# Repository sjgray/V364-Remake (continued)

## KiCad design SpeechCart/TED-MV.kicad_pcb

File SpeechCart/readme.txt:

Commodore V364 Prototype Remake Project   Steve J. Gray
=======================================

This is a project to remake the V364 prototype computer from Commodore.
This would have been the flagship model in the TED/264 series, and
would feature a larger case with numeric keypad and built-in speech
synthesis using a more integrated version of the Magic Voice cartridge
that was released for the C64.

Speech Cartridge
----------------

This is a cartridge to aid in development of the custom Gate Array chip
which this PCB will not work without. It uses the same circuit as the
V364 computer but is not guaranteed to be correct. It has a ROM socket
for development code and an audio jack for output via TRS cable. If not
plugged in audio will be routed thru the cartridge port and mixed with
the regular computer audio.

*** IMPORTANT!!!!!!!!! ***

This cart is untested! Use at own risk!!!!! Unless you are willing
to help with development of the custom gate array this PCB will be
of no use!

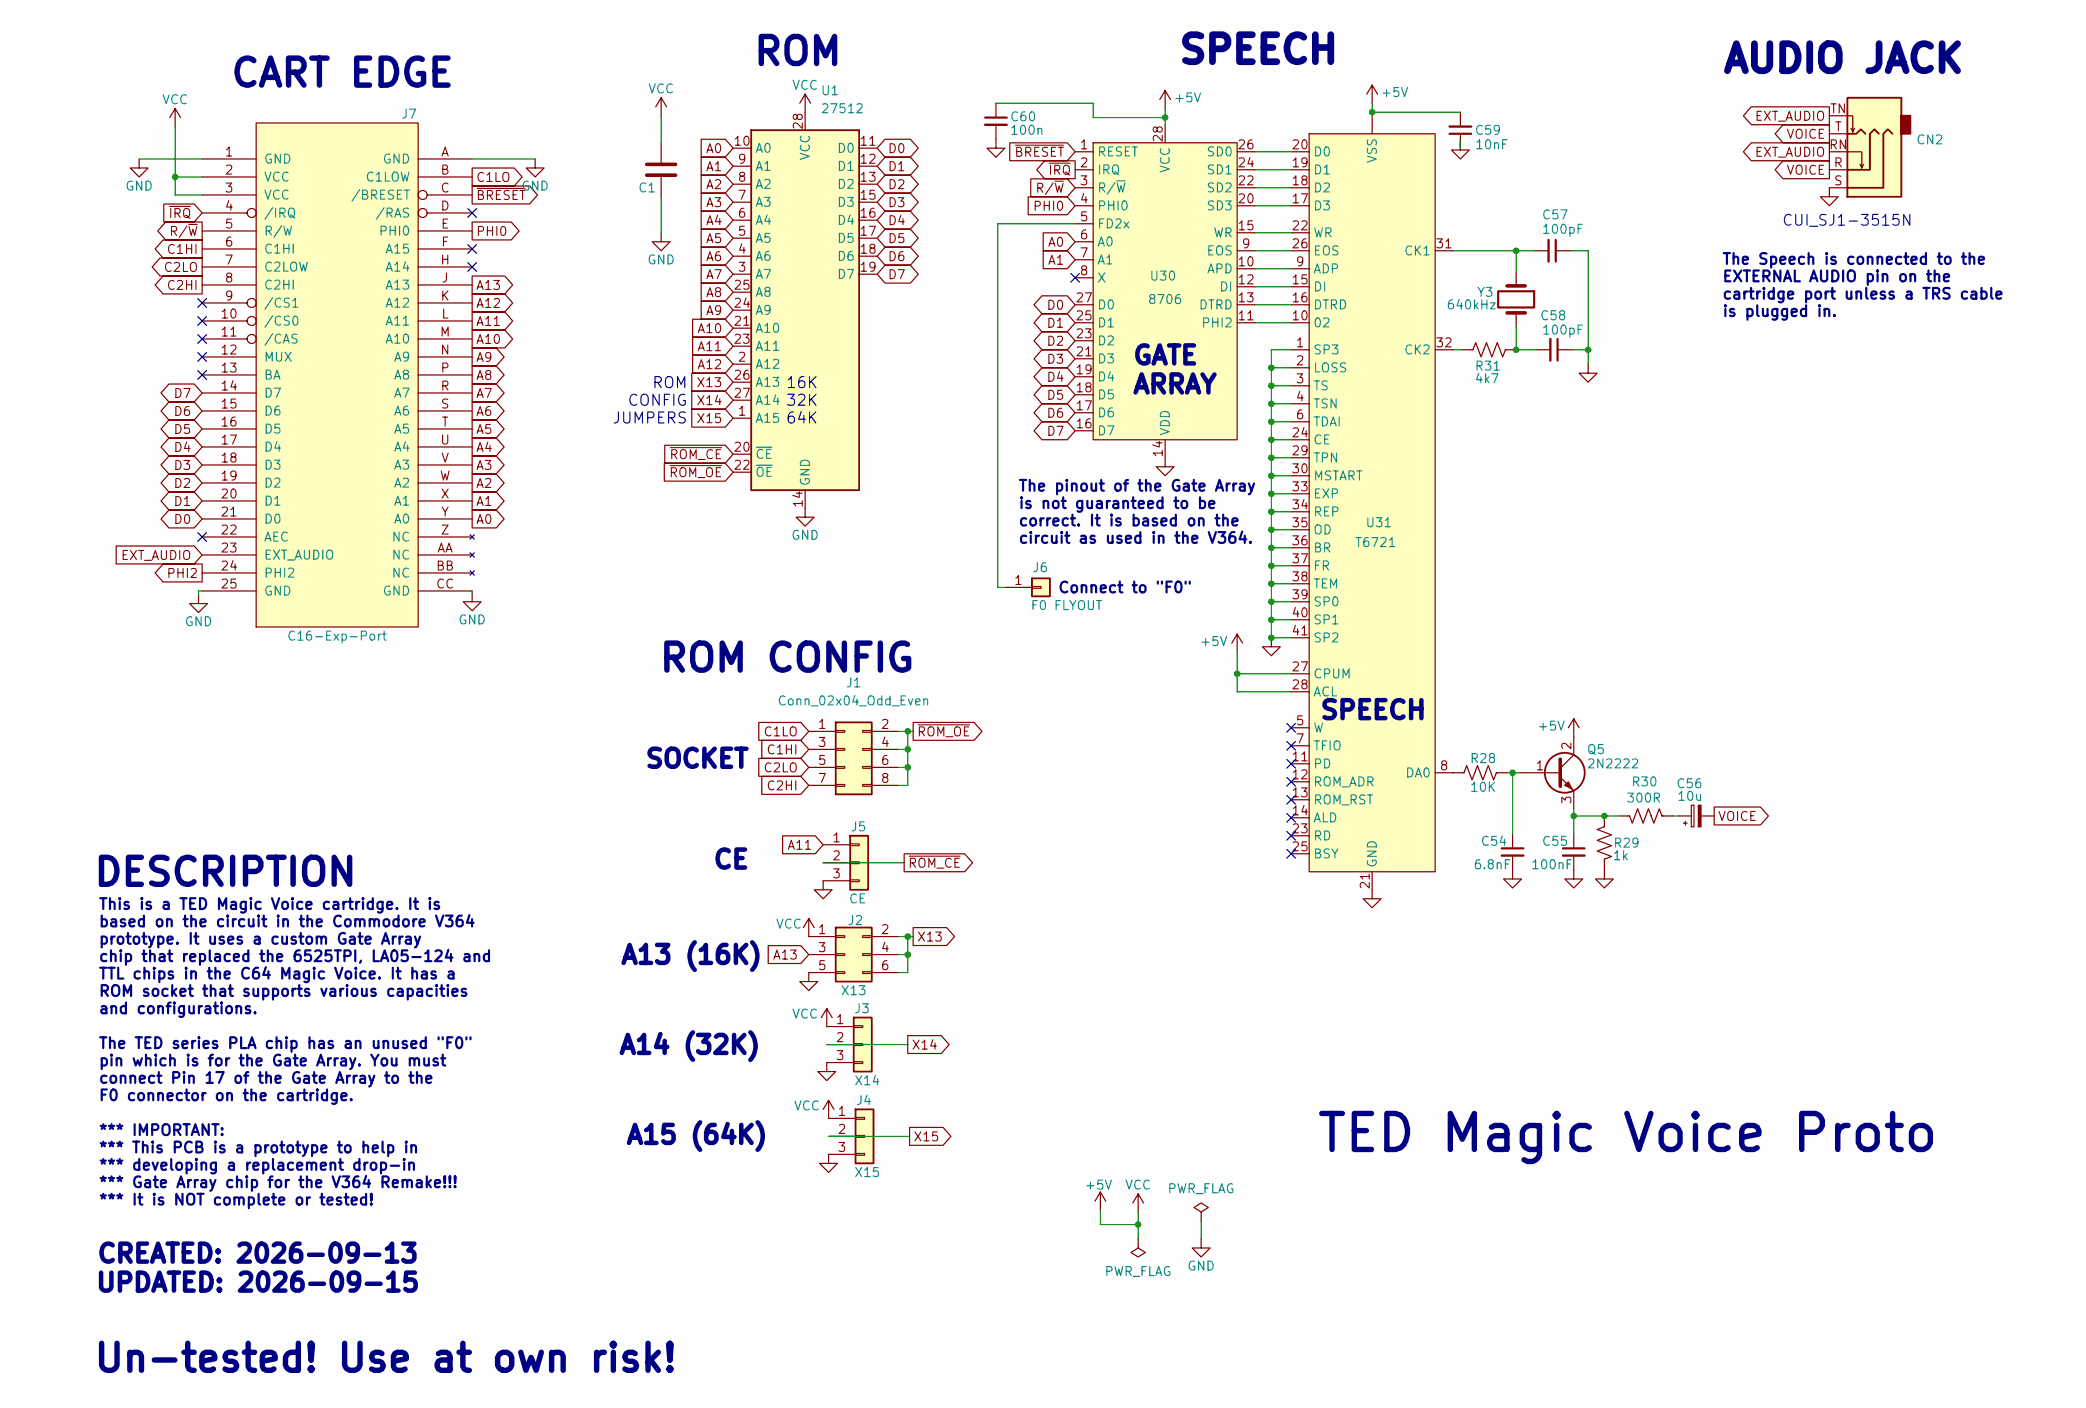
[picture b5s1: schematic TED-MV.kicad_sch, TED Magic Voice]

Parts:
C1: C; C_Disc_D5.0mm_W2.5mm_P5.00mm
C54: 6.8nF; C_Disc_D5.0mm_W2.5mm_P5.00mm
C55: 100nF; C_Disc_D5.0mm_W2.5mm_P5.00mm
C56: 10u; C_Disc_D5.0mm_W2.5mm_P5.00mm
C57, C58: 100pF; C_Disc_D5.0mm_W2.5mm_P5.00mm
C59: 10nF; C_Disc_D5.0mm_W2.5mm_P5.00mm
C60: 100n; C_Disc_D5.0mm_W2.5mm_P5.00mm
CN2: AUDIO_OUT; Jack_3.5mm_CUI_SJ1-3515N_Horizontal; MouserPN 490-SJ1-3525N
J1: Conn_02x04_Odd_Even; PinHeader_2x04_P2.54mm_Vertical
J2: X13; PinHeader_2x03_P2.54mm_Vertical
J3: X14; PinHeader_1x03_P2.54mm_Vertical
J4: X15; PinHeader_1x03_P2.54mm_Vertical
J5: CE; PinHeader_1x03_P2.54mm_Vertical
J6: F0 FLYOUT; PinHeader_1x01_P2.54mm_Vertical
J7: C16-Exp-Port; C16_Cart_Conn
Q5: 2N2222; TO-92_Inline_Wide
R28: 10K; R_Axial_DIN0204_L3.6mm_D1.6mm_P5.08mm_Horizontal
R29: 1k; R_Axial_DIN0204_L3.6mm_D1.6mm_P5.08mm_Horizontal
R30: 300R; R_Axial_DIN0204_L3.6mm_D1.6mm_P5.08mm_Horizontal
R31: 4k7; R_Axial_DIN0204_L3.6mm_D1.6mm_P5.08mm_Horizontal
U1: 27512; DIP-28_W15.24mm_LongPads
U30: 8706; DIP-28_W15.24mm_LongPads
U31: T6721; DIP-42_W15.24mm_Socket_LongPads
Y3: 640kHz; Crystal_HC18-U_Vertical

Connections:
+5V: C1.2, C59.2, C60.1, J2.1, J3.1, J4.1, J7.2 (VCC), J7.3 (VCC), Q5.2 (C), U1.28 (VCC), U30.28 (VCC), U31. (VSS), U31.27 (CPUM), U31.28 (ACL)
A0: J7.Y (A0), U1.10 (A0), U30.6 (A0)
A1: J7.X (A1), U1.9 (A1), U30.7 (A1)
A2: J7.W (A2), U1.8 (A2)
A3: J7.V (A3), U1.7 (A3)
A4: J7.U (A4), U1.6 (A4)
A5: J7.T (A5), U1.5 (A5)
A6: J7.S (A6), U1.4 (A6)
A7: J7.R (A7), U1.3 (A7)
A8: J7.P (A8), U1.25 (A8)
A9: J7.N (A9), U1.24 (A9)
A10: J7.M (A10), U1.21 (A10)
A11: J5.1, J7.L (A11), U1.23 (A11)
A12: J7.K (A12), U1.2 (A12)
A13: J2.3, J7.J (A13)
C1HI: J1.3, J7.6 (C1HI)
C1LO: J1.1, J7.B (C1LOW)
C2HI: J1.7, J7.8 (C2HI)
C2LO: J1.5, J7.7 (C2LOW)
D0: J7.21 (D0), U1.11 (D0), U30.27 (D0)
D1: J7.20 (D1), U1.12 (D1), U30.25 (D1)
D2: J7.19 (D2), U1.13 (D2), U30.23 (D2)
D3: J7.18 (D3), U1.15 (D3), U30.21 (D3)
D4: J7.17 (D4), U1.16 (D4), U30.19 (D4)
D5: J7.16 (D5), U1.17 (D5), U30.18 (D5)
D6: J7.15 (D6), U1.18 (D6), U30.17 (D6)
D7: J7.14 (D7), U1.19 (D7), U30.16 (D7)
EXT_AUDIO: CN2.RN, CN2.TN, J7.23 (EXT_AUDIO)
GND: C1.1, C54.2, C55.2, C57.1, C58.1, C59.1, C60.2, CN2.S, J2.5, J3.3, J4.3, J5.3, J7.1 (GND), J7.25 (GND), J7.A (GND), J7.CC (GND), R29.2, U1.14 (GND), U30.14 (VDD), U31.1 (SP3), U31.2 (LOSS), U31.3 (TS), U31.4 (TSN), U31.6 (TDAI), U31.21 (GND), U31.24 (CE), U31.29 (TPN), U31.30 (MSTART), U31.33 (EXP), U31.34 (REP), U31.35 (OD), U31.36 (BR), U31.37 (FR), U31.38 (TEM), U31.39 (SP0), U31.40 (SP1), U31.41 (SP2)
unnamed: C56.1, R30.2
unnamed: C58.2, R31.2, Y3.2
unnamed: J6.1 (Pin_1_1), U30.5 (FD2x)
unnamed: C54.1, Q5.1 (B), R28.1
unnamed: C55.1, Q5.3 (E), R29.1, R30.1
unnamed: U30.10 (APD), U31.9 (ADP)
unnamed: U30.12 (DI), U31.15 (DI)
unnamed: U30.13 (DTRD), U31.16 (DTRD)
unnamed: U30.9 (EOS), U31.26 (EOS)
unnamed: U30.11 (PHI2), U31.10 (02)
unnamed: U30.26 (SD0), U31.20 (D0)
unnamed: U30.24 (SD1), U31.19 (D1)
unnamed: U30.22 (SD2), U31.18 (D2)
unnamed: U30.20 (SD3), U31.17 (D3)
unnamed: U30.15 (WR), U31.22 (WR)
unnamed: C57.2, U31.31 (CK1), Y3.1
unnamed: R31.1, U31.32 (CK2)
unnamed: R28.2, U31.8 (DA0)
PHI0: J7.E (PHI0), U30.4 (PHI0)
PHI2: J7.24 (PHI2)
R/~W: J7.5 (R/W), U30.3 (R/~W)
VOICE: C56.2, CN2.R, CN2.T
X13: J2.2, J2.4, J2.6, U1.26 (A13)
X14: J3.2, U1.27 (A14)
X15: J4.2, U1.1 (A15)
~BRESET: J7.C (/BRESET), U30.1 (RESET)
~IRQ: J7.4 (/IRQ), U30.2 (IRQ)
~ROM_CE: J5.2, U1.20 (~CE)
~ROM_OE: J1.2, J1.4, J1.6, J1.8, U1.22 (~OE)

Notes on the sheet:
This is a TED Magic Voice cartridge. It is based on the circuit in the Commodore V364 prototype. It uses a custom Gate Array chip that replaced the 6525TPI, LA05-124 and TTL chips in the C64 Magic Voice. It has a ROM socket that supports various capacities and configurations. The TED series PLA chi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
CART EDGE
CUI_SJ1-3515N
CREATED: 2026-09-13 UPDATED: 2026-09-15
ROM
SOCKET
ROM CONFIG JUMPERS
TED Magic Voice Proto
16K 32K 64K
A15 (64K)
A13 (16K)
A14 (32K)
ROM CONFIG
DESCRIPTION
SPEECH
GATE ARRAY
Un-tested! Use at own risk!
Connect to "F0"
The Speech is connected to the EXTERNAL AUDIO pin on the cartridge port unless a TRS cable is plugged in.
The pinout of the Gate Array is not guaranteed to be correct. It is based on the circuit as used in the V364.
AUDIO JACK

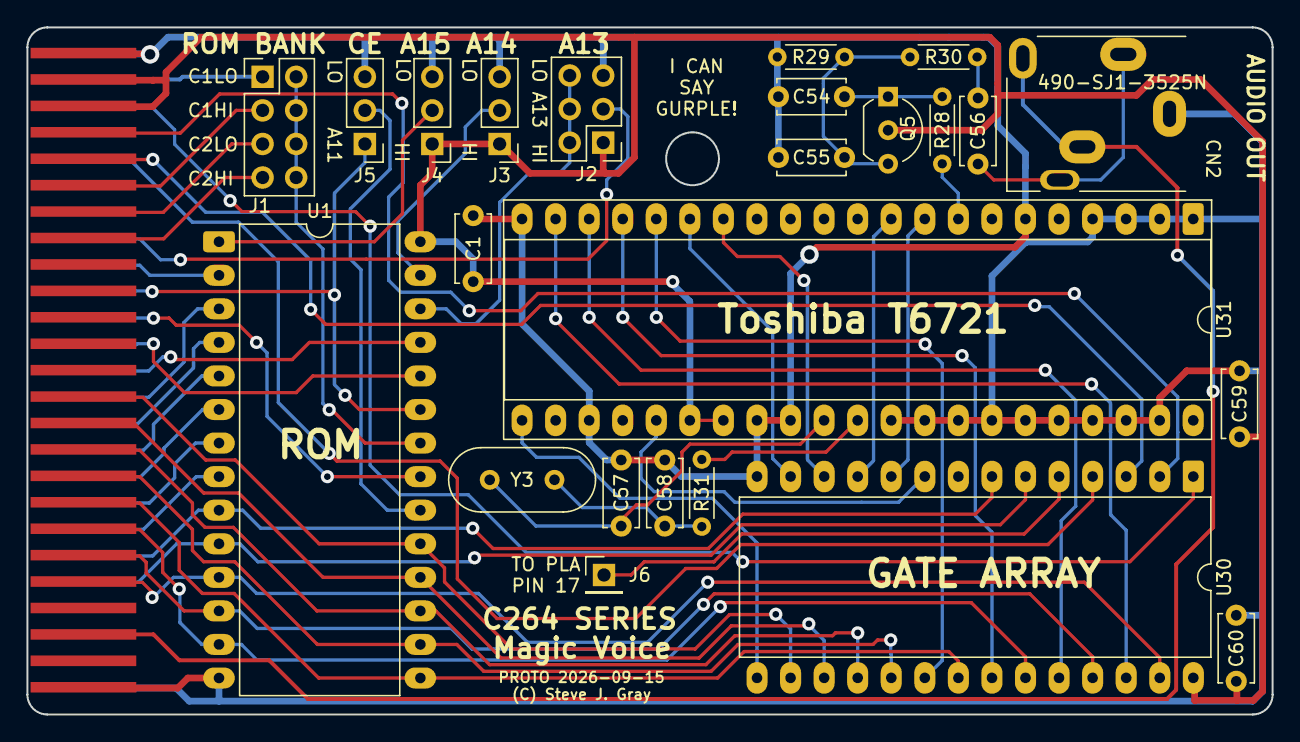
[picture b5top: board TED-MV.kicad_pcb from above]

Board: 2 copper layers, 94.2 x 52.0 mm, 25 parts (0 on the bottom side), 57 nets.
